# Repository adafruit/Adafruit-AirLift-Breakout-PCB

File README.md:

## Adafruit AirLift – ESP32 WiFi Co-Processor Breakout Board PCB

<a href="http://www.adafruit.com/products/4201"><br/>
Click here to purchase one from the Adafruit shop</a>

PCB files for the Adafruit AirLift – ESP32 WiFi Co-Processor Breakout Board. 

Format is EagleCAD schematic and board layout
* https://www.adafruit.com/product/4201

### Description

Give your plain ol' microcontroller project a lift with the Adafruit AirLift - a breakout board that lets you use the powerful ESP32 as a WiFi co-processor. You probably have your favorite microcontroller (like the ATmega328 or ATSAMD51), awesome peripherals and lots of libraries. But it doesn't have WiFi built in! So lets give that chip a best friend, the ESP32. This chip can handle all the heavy lifting of connecting to a WiFi network and transferring data from a site, even if its using the latest TLS/SSL encryption (it has root certificates pre-burned in).

Having WiFi managed by a separate chip means your code is simpler, you don't have to cache socket data, or compile in & debug an SSL library. Send basic but powerful socket-based commands over 8MHz SPI for high speed data transfer. You can use 3V or 5V Arduino, any chip from the ATmega328 or up, although the '328 will not be able to do very complex tasks or buffer a lot of data. It also works great with CircuitPython, a SAMD51/Cortex M4 minimum required since we need a bunch of RAM. All you need is an SPI bus and 2 control pins plus a power supply that can provide up to 250mA during WiFi usage.

We placed an ESP32 module on a PCB with level shifting circuitry, a 3.3V regulator, and a tri-state chip for MOSI so you can share the SPI bus with other devices. Comes fully assembled and tested, pre-programmed with ESP32 SPI WiFi co-processor firmware that [you can use in CircuitPython to use this into a WiFi co-processsor over SPI + 2 pins](https://github.com/ladyada/Adafruit_CircuitPython_ESP32SPI). We also toss in some header so you can solder it in and plug into a solderless breadboard.

[The firmware on board is a slight variant of the Arduino WiFiNINA core, which works great!](https://github.com/adafruit/nina-fw) At this time connection to Enterprise WiFi is not yet supported.

[Check out our learning system guide for schematics, files, and to get started AirLift'in' within minutes!](https://learn.adafruit.com/adafruit-airlift-breakout)

### License

Adafruit invests time and resources providing this open source design, please support Adafruit and open-source hardware by purchasing products from [Adafruit](https://www.adafruit.com)!

Designed by Limor Fried/Ladyada for Adafruit Industries.

Creative Commons Attribution/Share-Alike, all text above must be included in any redistribution. See license.txt for additional details.

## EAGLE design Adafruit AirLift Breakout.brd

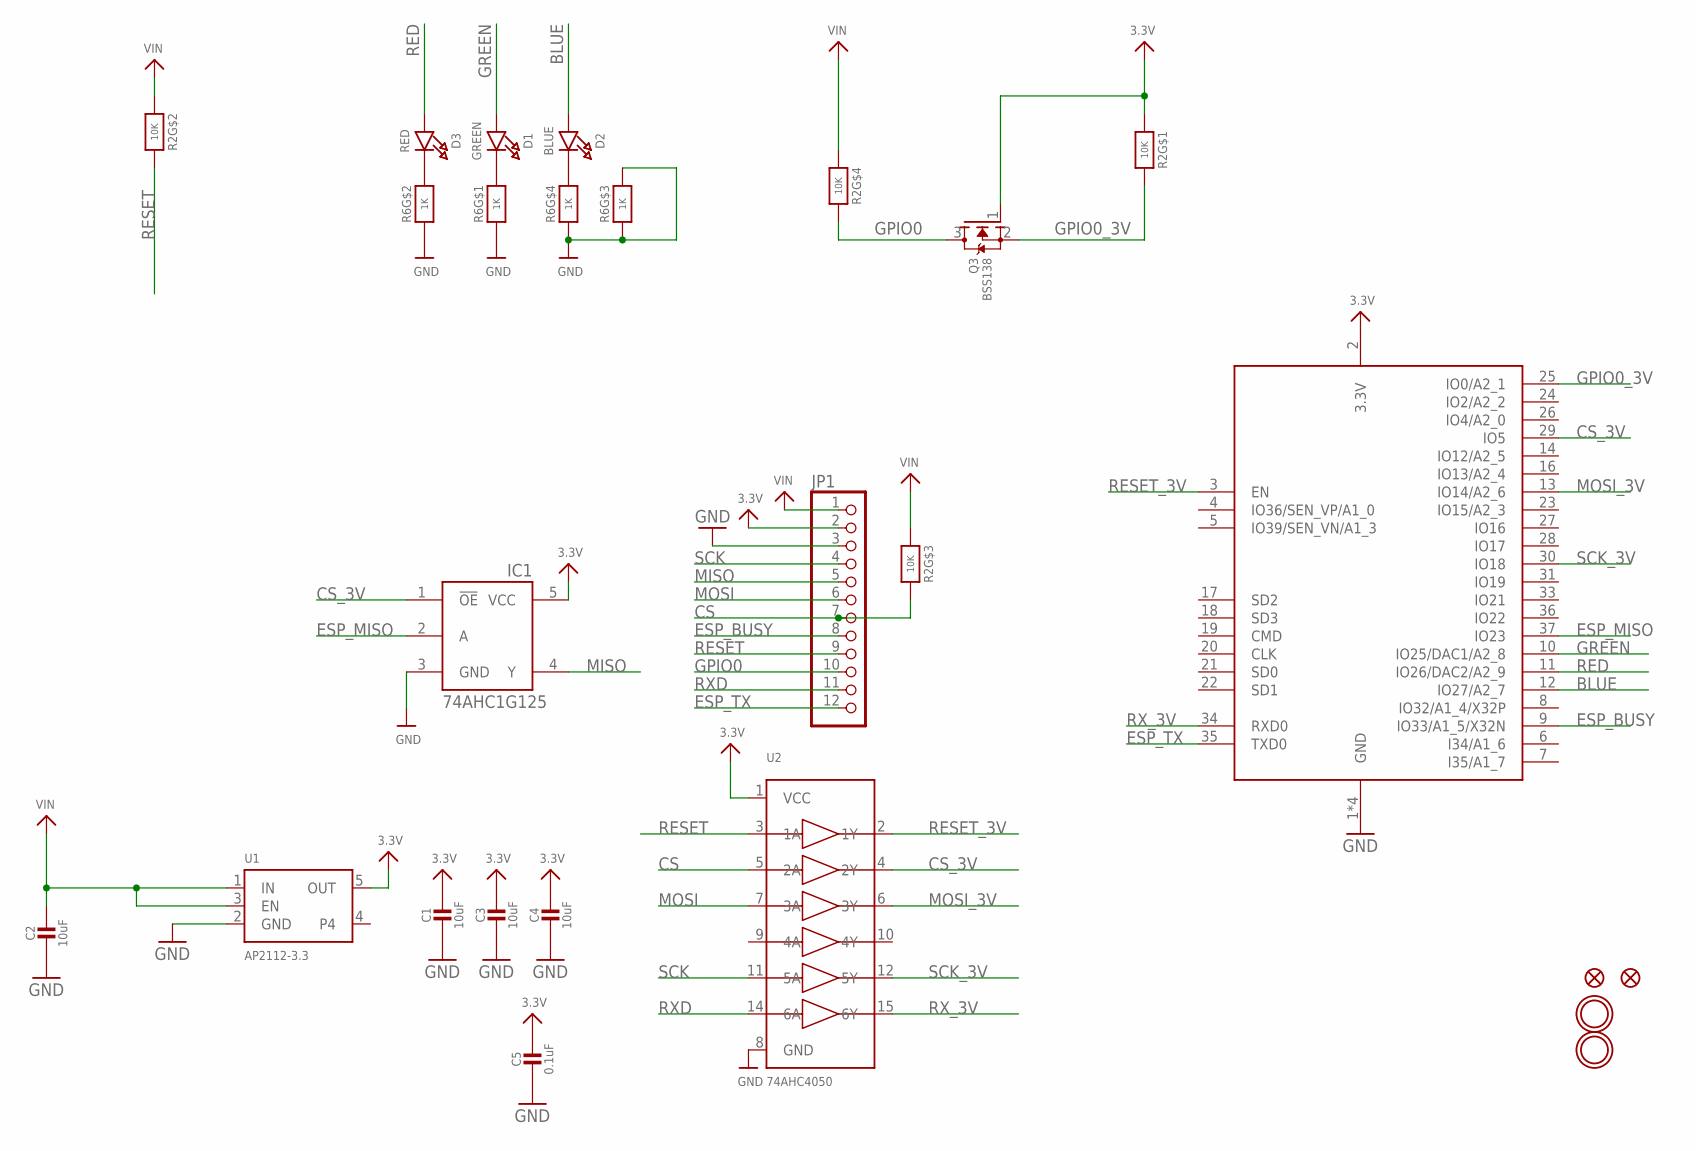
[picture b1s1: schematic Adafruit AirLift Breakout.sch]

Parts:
C1, C2, C3, C4: 10uF; 0805-NO
C5: 0.1uF; 0603-NO
D1: GREEN; CHIPLED_0603_NOOUTLINE
D2: BLUE; CHIPLED_0603_NOOUTLINE
D3: RED; CHIPLED_0603_NOOUTLINE
FID1, FID3: FIDUCIAL_1MM
IC1: 74AHC1G125; SOT23-5L
JP1: HEADER-1X12; 1X12_ROUND
Q3: BSS138; SOT23-WIDE
R2: 10K; RESPACK_4X0603
R6: 1K; RESPACK_4X0603
U1: AP2112-3.3; SOT23-5
U2: 74AHC4050; TSSOP16
U$15, U$16: MOUNTINGHOLE2.5; MOUNTINGHOLE_2.5_PLATED
X1: ESP32_WROOM32; WROOM32

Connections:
3.3V: C1.1, C3.1, C4.1, C5.1, IC1.5 (VCC), JP1.2, Q3.1 (G), R2.8 (2), U1.5 (OUT), U2.1 (VCC), X1.2 (3.3V)
BLUE: D2.A, X1.12 (IO27/A2_7)
CS: JP1.7, R2.6 (2), U2.5 (2A)
CS_3V: IC1.1 (!OE), U2.4 (2Y), X1.29 (IO5)
ESP_BUSY: JP1.8, X1.9 (IO33/A1_5/X32N)
ESP_MISO: IC1.2 (A), X1.37 (IO23)
ESP_TX: JP1.12, X1.35 (TXD0)
GND: C1.2, C2.2, C3.2, C4.2, C5.2, IC1.3 (GND), JP1.3, R6.1, R6.2 (1), R6.3 (1), R6.4 (1), R6.6 (2), U1.2 (GND), U2.8 (GND), X1.1 (GND), X1.15 (GND), X1.38 (GND), X1.P$1 (GND)
GPIO0: JP1.10, Q3.3 (D), R2.4 (1)
GPIO0_3V: Q3.2 (S), R2.1, X1.25 (IO0/A2_1)
GREEN: D1.A, X1.10 (IO25/DAC1/A2_8)
MISO: IC1.4 (Y), JP1.5
MOSI: JP1.6, U2.7 (3A)
MOSI_3V: U2.6 (3Y), X1.13 (IO14/A2_6)
unnamed: D3.C, R6.7 (2)
unnamed: D1.C, R6.8 (2)
unnamed: D2.C, R6.5 (2)
RED: D3.A, X1.11 (IO26/DAC2/A2_9)
RESET: JP1.9, R2.7 (2), U2.3 (1A)
RESET_3V: U2.2 (1Y), X1.3 (EN)
RXD: JP1.11, U2.14 (6A)
RX_3V: U2.15 (6Y), X1.34 (RXD0)
SCK: JP1.4, U2.11 (5A)
SCK_3V: U2.12 (5Y), X1.30 (IO18)
VIN: C2.1, JP1.1, R2.2 (1), R2.3 (1), R2.5 (2), U1.1 (IN), U1.3 (EN)

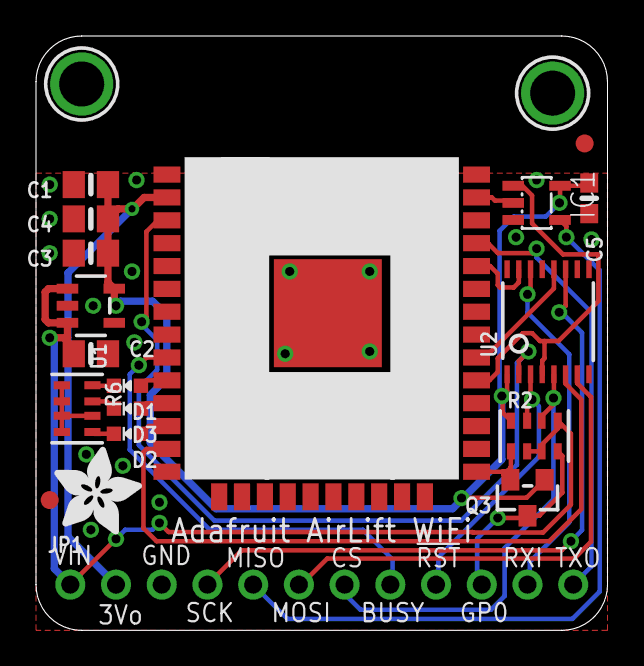
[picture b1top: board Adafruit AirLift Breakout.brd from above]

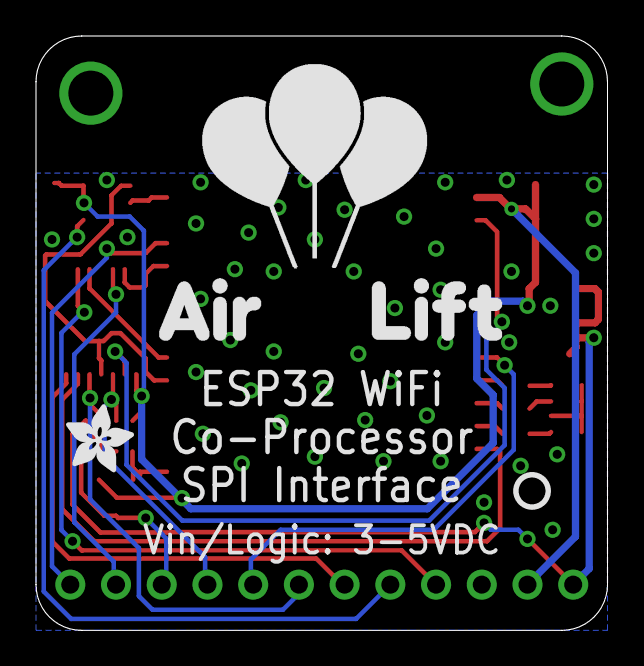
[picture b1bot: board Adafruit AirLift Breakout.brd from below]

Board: 2 copper layers, 31.8 x 33.0 mm, 24 parts (3 on the bottom side), 25 nets.

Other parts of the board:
U$2: ADAFRUIT_3.5MM
U$13: PCBFEAT-REV-040
U$21: ADAFRUIT_5MM
U$24: AIRLIFT

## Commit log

2019-04-10 Adding PCB files
2019-07-17 updated to use cookiecutter for pcb repos

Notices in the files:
parts and their libraries:
microbuilder: This work is placed in the public domain, and may be freely used for commercial and non-commercial work with the following conditions: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
